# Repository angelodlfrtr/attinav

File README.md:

# Attinav

**Work in progress.** A precision attitude sensor module for cave survey: static "point and
shoot" azimuth and inclination to 0.1°, with the redundancy to tell a good shot from a disturbed
one. This repository covers the sensor module only. The carrier (display, battery, BLE), the laser
and the housing are separate.

## Status

| part | state |
|---|---|
| Hardware Rev B | schematic complete, PCB WIP |
| Firmware | builds, lints and tests clean, never run on hardware |
| Desktop client | builds, lints and tests clean against the built-in simulator, not yet run against hardware |

## Hardware (Rev B)

- STM32U575RGT6 (Cortex-M33, 160 MHz, 1 MiB flash, 768 KiB SRAM)
- 3 × PNI RM3100 magneto-inductive triads (gradiometer: nearby iron shows as disagreement)
- 2 × Murata SCA3300-D01 inclinometer-grade accelerometers
- TDK ICM-42688-P IMU as a motion gate during the integration window
- Pt1000 coil thermometers for temperature-compensated calibration
- USB-C to the host, 8-pin FFC (UART, power, `QUIET`) to the carrier

Design notes and error budget: `hardware/kicad/README.md`. Plan and decisions:
`hardware/kicad/ROADMAP.md`.

## Software

- `software/firmware` — Rust / Embassy firmware: shot engine, on-device Heeb/DistoX
  calibration (14 × 4 shots, up to four temperature sets), quality flags, binary protocol over
  USB CDC and the carrier UART, OTA update with rollback. `README.md`, `PROTOCOL.md`, `OTA.md`.
- `software/client` — Tauri v2 desktop client (React, Redux, Tailwind) to test, calibrate,
  visualise, configure and update the module. Includes a protocol-level simulator, so it runs
  without hardware. `README.md`.

Both projects have a Nix dev shell and a `Makefile`, the root `Makefile` delegates to them:

```sh
make help                            # targets
make check                           # formatting, lints, tests and builds of both projects
make -C software/firmware help
make -C software/client help
```

CI (`.github/workflows/ci.yml`) runs the same targets on every push and pull request, inside the
same Nix shells, plus actionlint and zizmor over the workflows (`make workflows`, root flake).

## License

- Software: AGPL-3.0-only
- Hardware design files: CERN-OHL-S-2.0

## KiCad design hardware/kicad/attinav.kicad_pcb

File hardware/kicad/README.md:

# Attinav hardware — design notes

Design review, error budget and Rev B architecture for the Attinav AHRS module.

**Application:** precise AHRS for cave survey (speleology). Static "point and shoot"
station measurement — azimuth + inclination — not dynamic attitude tracking.
This distinction drives almost every decision below.

**Status:** Rev A reviewed 2026-09-20. Three functional bugs found (see
[Rev A defects](#rev-a-defects)). Rev B architecture proposed but not implemented.

---

## Table of contents

- [Rev A defects](#rev-a-defects)
- [Tooling caveats](#tooling-caveats)
- [Requirements and error budget](#requirements-and-error-budget)
- [Sensor selection rationale](#sensor-selection-rationale)
- [Rev B architecture](#rev-b-architecture)
- [Magnetic hygiene rules](#magnetic-hygiene-rules)
- [System integration](#system-integration)
- [Calibration](#calibration)
- [References](#references)

---

## Rev A defects

Verified against a kicad-cli generated netlist and PCB geometry, not from audit tools.

### Critical — functional bugs

**1. D1/D2 Schottky pair has a floating common node**

`Net-(D1-K)` connects only `D1.K` and `D2.K` — nothing else. D1 is A=GND/K=node,
D2 is A=+3.3V_EXT/K=node. As drawn the pair conducts nothing and protects nothing.

Placement (D1 85.9,138.4; D2 83.3,138.4; near Q1 80.0,134.4 and R4) suggests it was
intended as a rail clamp on `/EN`, which is otherwise a bare MOSFET gate exposed on
J3.12 and J4.2. Note D2's orientation (anode on +3.3V_EXT) is a feed diode, not a
clamp — a positive clamp needs anode on the signal, cathode on the rail.

**2. BOOT0 boot-select jumper is defeated**

NT1 (`NetTie-2_SMD_Pad0.5mm`) hard-shorts `Net-(U1-BOOT0)` to GND with 0 Ω copper.
J1 (pin 2 = +3.3V) feeds BOOT0 through R1 4.7k. Shorting J1 puts 4.7k across a dead
short; BOOT0 stays at ~0 V and never reaches VIH. DFU/system-bootloader entry is
impossible.

*Fix:* replace NT1 with a 10k pull-down. Then check the divider — 4.7k/10k gives only
~2.24 V, so drop R1 to ~1k for margin.

**3. Crystal load caps wrong**

Y1 = YXC **X50328MSB2GI**, 8 MHz, **CL = 20 pF** (confirmed via JLCPCB DB, LCSC
C115962). Required load caps:

```
C = 2 x (CL - Cstray) = 2 x (20 - 4) ~= 33 pF
```

Fitted: **20 pF** (C15/C16) → effective CL ≈ 14 pF. An under-loaded crystal runs
fast, roughly **+60 ppm**, far outside the crystal's own ±10/±20 ppm spec.

*Fix:* C15/C16 → 33 pF.

### Warnings

**4. STM32 (U1) has no local decoupling.** Measured pad-to-pad on the PCB:

| Pin | Nearest same-net cap |
|---|---|
| U1.24 VDD | C11 @ **16.7 mm** |
| U1.36 VDD | C11 @ **10.6 mm** |
| U1.48 VDD | C9 @ **11.9 mm** |
| U1.9 VDDA/VREF+ | C13 @ **11.2 mm** |
| U1.22 VCAP1 | C2 @ 2.26 mm — OK |

C9/C12/C13/C14 sit at x≈78 mm on the left board edge; U1 is at x=93.3 mm — opposite
edges of a 30.5 mm-wide board. Partly mitigated by the stackup (In2 = +3.3V plane,
In3 = GND at 0.1 mm → good plane capacitance), but 100 nF per VDD pin within ~3 mm
is standard practice.

By contrast **U2 (SCHA63T) is done correctly** — all 8 supply pins have caps at
~3.2 mm. The oversight is on U1/U3/U5 only.

VDDA/VREF+ (pin 9) also has no dedicated filtering (no ferrite, no 1 µF + 10 nF).
PB0 is an ADC input reading the LM94021, so this matters.

**5. U3 (RM3100) has no decoupling and no plane.** Nearest +3.3V cap is **24 mm**.
U3 sits at (91.4, 90.4), inside a copper-pour keepout spanning Y 81.28–102.362 on
**all six layers** — deliberate for magnetic cleanliness, but see
[Magnetic hygiene rules](#magnetic-hygiene-rules): this is probably backwards.
Its supply is thin traces only (+3.3V 12.3 mm, GND 9.1 mm, both single-layer F.Cu)
with no local charge reservoir, and the RM3100 is magneto-inductive — it actively
pulses current through its coils.

**6. U5 (TPL5010) 17.3 mm, U4 (LM94021) 5.8 mm** from nearest cap. Both datasheets
call for a local 100 nF.

**7. U1 VBAT (pin 1) floating**, flagged no-connect. ST guidance for STM32F4 is to
tie VBAT to VDD with a 100 nF when no backup battery is used.

**8. No bulk capacitance or protection on +3.3V_EXT.** It arrives on J2.2/J3.3 and
feeds only Q1.S, R4, D2.A — no capacitor at all. C14 is downstream of the PMOS, so
Q1 turn-on dumps inrush into ~13 µF with no gate RC for soft-start.

**9. `/EN` is a bare MOSFET gate on two connectors** (J3.12, J4.2) with only a 10k
pull-up — no series resistor, no ESD clamp (and see defect 1).

### Minor

- **C14 value string wrong**: reads `10uF/50V/20%/XYR/0603`; LCSC C96446 is actually
  Samsung CL10A106MA8NRNC = **10 µF 25 V X5R 0603**. Ordered part is correct and fine
  for 3.3 V; the text has a wrong voltage and a typo ("XYR"). Check C9/C12/C13
  ("50V" → C14663) the same way.
- **U3 has no LCSC/MPN**, and its Datasheet property points to a witmotion.com store
  page for a JY-RM3100 *module*, not the PNI RM3100 datasheet. Also behind the one
  real DRC warning: *"Footprint 'WIT-RM3100' does not match copy in library
  'WIT-rm3100'"*. Resolve before fab.
- **U2 uses property name `MP` not `MPN`** — breaks BOM tooling.
- **Mounting holes inconsistent**: H3 pad tied to GND; H1/H2/H4 explicitly no-connect
  (floating copper).
- **D4 power LED draws ~0.75 mA continuously** on a board built around a 35 nA TPL5010.
- Global `min_clearance`/`min_track_width` are 0.0 in the project, though the Default
  netclass sets 0.2 mm / 0.25 mm so DRC is still meaningful.

### Rev A verified good

- 0 ERC errors, 0 DRC errors, fully routed. No shorted nets. All 12 single-node nets
  are explicit no-connects.
- Geometry fab-friendly: 0.25/0.7 mm tracks, 0.3/0.5 mm via drills, 0.25 mm min pad
  (QFN48 0.5 mm pitch), ~1.6 mm 6-layer stackup.
- Q1 PMOS correctly oriented as high-side switch (S=input, D=load, gate pulled to
  source → default off).
- NRST: 100 nF (C1) + button + internal pull-up per ST guidance; TPL5010 reset gated
  by open solder jumper JP1 (intentional).
- Stackup well considered: In2 (+3.3V) / In3 (GND) 0.1 mm apart for plane capacitance.

---

## Tooling caveats

Konnect MCP audit results on this project are unreliable. Do not trust them without
verification:

- **`run_design_review` verdict "NOT READY"** rests entirely on 7 false decoupling
  errors. It reads **0 pads** from the board and finds only 7 of ~20 power pins.
- **`audit_decoupling`** reports "0/7 power pins have decoupling" while the netlist
  shows 5× 100 nF + 2× 1 µF + 10 µF on +3.3V. It needs board pads for its proximity
  check and silently degrades to "no cap found".
- **`find_orphan_items`: 261 "dangling wire ends"** — all false. Verified
  (81.28, 45.72) is U1 pin 7 (NRST) with a wire correctly landing on it. The tool
  does not resolve pin positions.
- **`get_component_nets` / `trace_from_point` return `net: null`** for pins whose net
  comes from a power symbol rather than a label. They resolve nets from labels only.
- **155 ERC + 45 DRC warnings** were all "library not found / not enabled". Root cause
  (found 2026-11-01): the Konnect MCP server entry in `~/.claude.json` hardcodes
  `KICAD10_SYMBOL_DIR` / `KICAD10_FOOTPRINT_DIR` as Nix store paths, which go stale at
  every rebuild that bumps `kicad-symbols` / `kicad-footprints`. Konnect also does not
  follow KiCad 10's nested `(type "Table")` entry in the user's global lib tables, so
  it had no fallback. **Durable fix (2026-11-02):** the server now starts through
  `sh -c 'eval "$(grep -E "^export KICAD10_(SYMBOL|FOOTPRINT|TEMPLATE|3DMODEL)_DIR=" /run/current-system/sw/bin/kicad-cli)"; exec "$0" "$@"' konnect`,
  reading the current paths from the kicad-cli wrapper at every start. Separately, the
  user's global `sym-lib-table` / `fp-lib-table` held only KiCad 10's nested
  `(type "Table")` entry, which KiCad resolves but Konnect does not follow; they
  were replaced with the flat stock tables (every library via
  `${KICAD10_SYMBOL_DIR}` / `${KICAD10_FOOTPRINT_DIR}`, no store paths). A future KiCad
  release that adds stock libraries needs the template tables copied again. Symptom when it recurs: every stock `lib_id` fails with "no library
  'Device' in the project or global sym-lib-table". Symbols still resolve from the
  embedded cache, so 0-error results on existing sheets remain genuine.

**Reliable method:** generate a real netlist with `kicad-cli` and parse it, and parse
`.kicad_pcb` directly for geometry. Note KiCad 10 writes pad nets as `(net "NAME")`
with no net number — index `[1]`, not `[2]`.

### Konnect schematic-building notes (v0.13.0, learned on the mag sheet)

- **Subagents bind to the Konnect server process alive at spawn.** After an MCP
  reconnect, an already-spawned agent keeps talking to the old process (stale env, old
  toolsets). Respawn agents after any reconnect; never let two agents write one sheet.
- `register_*_library` with global scope **writes into `~/.config/kicad/10.0/*-lib-table`**
  and there is no unregister tool. Do not let agents probe library paths this way.
- `annotate_schematic` must run on the **file that owns the symbols** (child sheet); on
  the root it no-ops. Place with `?` references — explicit numbers are kept and defeat
  per-instance numbering on multi-instanced sheets.
- `move_schematic_component` refuses symbols once they carry multi-instance paths; use
  `move_region`. `edit_sheet` resize does not move sheet pins — re-place them with
  `edit_sheet_pin`, then `validate_sheet_pins`.
- Sheet boxes and pins must land on the 1.27 mm grid or every pin raises
  `endpoint_off_grid`; `batch_delete` by UUID is the only way to remove free text.
- **`kicad-cli sch erc` does not report duplicate reference designators across sheets.**
  A sheet annotated in isolation (MCU sheet, 2026-11-01: U1, R1, C1… colliding with the mag
  and power sheets) passed ERC clean while the netlist merged pins of different parts.
  After every annotation, parse the netlist `(components …)` block and assert every `ref`
  is unique; `annotate_schematic` must be run with the project context so other sheets'
  numbers are reserved.
- `render_schematic_png` without `output` drops a PNG next to the schematic; always pass
  a scratch path. A wire routed straight through a foreign pin silently creates a
  junction (`find_shorted_nets` cannot see unnamed nets) — check coil nodes with
  `trace_from_point` and the `kicad-cli` netlist.

---

## Requirements and error budget

**Target:** 0.1° azimuth, 0.05° inclination. Roughly 2–5× better than a DistoX2.

### The binding constraint

For a tilt-compensated compass, **tilt error is amplified into azimuth error by
tan(magnetic dip)**. At European dip (~63°), tan = **1.96**.

> **The accelerometer must be ~2× better than the azimuth target.**
> For 0.1° azimuth you need ~0.035° of tilt = **0.6 mg**.

This makes the accelerometer, not the magnetometer, the hard problem.

### Field error to heading error

```
heading error (rad) ~= dB / H        H ~= 20 uT horizontal (mid-latitude Europe)

0.1 deg  =>  dB < 35 nT
0.5 deg  =>  dB < 175 nT
```

### Budget

| Term | Contribution |
|---|---|
| Mag noise (3× RM3100, averaged ~5 nT) | 0.014° |
| Mag calibration residual (~20 nT) | 0.057° |
| Tilt error 0.035° × tan 63° | 0.069° |
| Mag↔accel frame misalignment residual | 0.030° |
| Sight-axis alignment | 0.030° |
| **RSS azimuth** | **≈ 0.10°** |
| SCA3300 Mode 4 noise (0.15 mg) | 0.009° |
| Accel offset after temp cal (~1 mg) | 0.057° |
| **RSS inclination** | **≈ 0.05°** |

Nothing here works on factory specs. Per-unit calibration is mandatory.

---

## Sensor selection rationale

### Why the gyro does not buy azimuth

A gyro only replaces the compass if it can **gyrocompass** — resolve Earth's rotation
(15.04°/hr). At 45° latitude the horizontal Earth rate is ~10.6°/hr, so 0.5° of
azimuth needs gyro bias stability around **0.1°/hr**. MEMS parts, SCHA63T included,
are one to two orders of magnitude away.

What a gyro *does* buy:
- Motion/stillness gating during a shot
- **Short attitude transfer** through a magnetically disturbed station. At ~0.28°/√hr
  ARW, carrying azimuth for 1 minute costs ~0.036° — genuinely useful, and a cheap
  part does it. **Do not pay €200 for SCHA63T to do this.**

### Why 3× sensors — and why not for precision

Averaging N sensors cuts *uncorrelated random* error by √N. Three gives 1.73×.
But the design is **not noise-limited**: the RM3100 detects 2.7 nT at 1 Hz, which at
20 µT horizontal is under 0.05° of azimuth noise — already 10× below target.

And **time-averaging is free**: the measurement is static, so 100 samples at 100 Hz
buys √100 = 10× with zero hardware, versus √3 = 1.7× for three chips. Or raise the
RM3100 cycle count.

**The real reasons for redundancy** (and what BRIC5 does — 2× SCA3300-D01 plus
redundant magnetometers, explicitly *"to detect calibration drift, malfunctions, and
magnetic gradients"*):

- **Magnetic gradiometry — of *nearby* iron.** A uniform Earth field reads identically at
  all sensors. Nearby iron — magnetite in the rock beside you, a bolt, a steel carabiner —
  creates a *gradient*. Spatially separated magnetometers that disagree after calibration
  flag the station as disturbed. DistoX users guess at this; measuring it is a real
  capability upgrade.
  **Blind spot:** a large *distant* mass — a steel gate 3 m away, an iron-bearing stratum —
  produces a nearly uniform offset with negligible gradient, and gradiometry cannot see it.
  That case is caught only by the **|B|-vs-IGRF and dip-vs-IGRF** checks. Gradiometry is
  one of three anomaly detectors, not *the* detector.
- **Blunder detection.** You cannot redo a trip.
- **2 detects disagreement; 3 lets you vote** and identify which sensor is wrong.

### Why 3× cheap sensors will NOT work

Averaging fixes *random* error. Cheap sensors fail on *systematic* error:

- Cheap magnetometers (AMR: QMC/HMC5883, LIS3MDL; Hall: BMM150/BMM350) suffer
  hysteresis, nonlinearity and temperature-dependent offset. Three identical parts on
  one board at one temperature drift **the same way** — correlated, so √N does nothing.
- AMR parts need set/reset degauss pulses; miss them and one strong field leaves a
  permanent bias.
- The RM3100's advantage was never noise — it's **linearity, no hysteresis, and gain
  stability**. Averaging cannot recover those.

**3× cheap ≠ 1× good.**

### Why not the DRV425 fluxgate

Verified against the DRV425 datasheet (Rev B, Oct 2025):

| Parameter | Value |
|---|---|
| Noise, **0.1–10 Hz** (compass band) | **17 nT RMS** |
| Noise density @ 1 kHz | 1.5 nT/√Hz |
| Offset | ±2 µT typ, ±8 µT max |
| **Offset drift** | **±5 nT/°C** |
| Gain drift | ±7 ppm/°C |
| Gain error | ±0.04% |
| Linearity error | 0.1% |
| Hysteresis (after ±10 mT sweep) | 1.4 µT |
| Quiescent current | 6 mA typ, 8 mA max @ 3.3 V |
| Compensation loop active after power-on | 70 µs |

The headline 1.5 nT/√Hz is **at 1 kHz** and irrelevant to a compass. The
compass-band figure of 17 nT RMS essentially **ties** the RM3100.

**Power is not the obstacle** — the 70 µs startup makes duty-cycling trivial
(~120 µA average for 3 axes at one shot/minute).

**Offset drift is the obstacle.** ±5 nT/°C gives 0.14° per 10 °C, or 0.27° across a
surface-to-cave transient (25 °C → 6 °C). It is a *magnetic* offset, so no
improvement in electronics touches it. And what closed-loop buys — superb gain
stability — is not what limits a compass, since heading comes from `atan2` of ratios
where common gain error largely cancels.

To beat the RM3100 you would need anti-parallel sensor pairs (6 parts, back-to-back
across the PCB so the sensitive axis reverses), a high-value shunt (~440 Ω instead of
22 Ω, trading the unused ±2 mT range for 20× lower amplifier drift contribution), a
ratiometric multiplexed 24-bit ADC chain, a temperature-stable perpendicular Z mount,
and sequenced duty-cycled power. Not worth it.

**Where the DRV425 would win:** as a dedicated gradiometer, because ±0.04% gain error
and ±7 ppm/°C gain drift mean two parts subtract very cleanly, and a gradiometer only
cares about the difference *changing*. Not needed here — 3× RM3100 already gives
gradiometry.

### RM3100 form factor — important

The RM3100 is a **discrete chipset, not a single package**:

| Component | Size | Qty per suite |
|---|---|---|
| SEN-XY | 6 × 2.1 × 2.21 mm | 2 |
| SEN-Z | 3.88 × 2.98 × **6.35 mm tall** | 1 |
| MagI2C ASIC | 4 × 4 × 0.75 mm, 28-pin MLF | 1 |

- MagI2C must sit **within 10 cm** of the coils.
- **You place the coils, so orthogonality is your responsibility.** PNI specifies a
  5 mil stencil with paste area much smaller than the pad, specifically to limit
  SEN-Z tilt — tilt maps directly to axis misalignment error.
- **SEN-Z is a vertical solenoid that senses the board-normal axis while being
  reflow-soldered flat.** No perpendicular daughtercard. This is the decisive
  advantage over any single-axis in-plane sensor such as the DRV425.
- No successor exists — there is no RM3200. The only variant is **RM3100-CB**, a
  board-mounted vibration-hardened version (50 g RMS, MIL-STD-810H 514.8).

---

## Rev B architecture

| Role | Part | Qty | Rationale |
|---|---|---|---|
| Magnetometer | **PNI RM3100 sensor suite** | **3 sets** | No better option exists. 3 sets = spatial gradiometer + voting |
| Accelerometer | **Murata SCA3300-D01**, Mode 4 | **2** | 0.15 mg RMS, damped element, self-diagnostics. `\|a\|=1g` is a built-in third vote |
| Gyro (optional) | **TDK ICM-42688-P** | 1 | Short attitude transfer + motion gating only |
| Temp at mag coils | **Pt1000 RTD, non-magnetic package** | 3 | The platinum *element* is non-magnetic; **SMD thin-film RTDs often have Ni-barrier terminations** — specify verified non-magnetic terminations or a leaded element. Compensates **gain** tempco only: the MagI2C has no temperature sensor, and PNI states offset is drift-free |
| Temp at accel | **SCA3300 internal die sensor** (TMP117 ×0–1 as board reference only) | — | 18.9 LSB/°C → **0.053 °C resolution**, read in the same SPI frame. Its ±10 °C *absolute* offset is irrelevant — compensation uses a per-unit curve against the reported value. Die temperature is the **correct** variable; an external sensor lags and misses package gradients |
| MCU | **STM32U575RGT6** (LQFP-64, non-Q: LDO only, VCAP; LCSC C5270980). **STM32U585RIT6 is pin-identical** (adds crypto accelerators and 1 MB flash) and stays the drop-in upgrade | 1 | see below — the section is written for the U585; everything applies to the U575 except the crypto peripherals |
| Regulator | **TPS7A2033PDBVR** (300 mA, 7 µVrms, high PSRR; LCSC C2862740, genuine TI only), **EN pin = the FFC `EN` line, high = on**, 100 k pull-down, bench jumper to `+5V` | 1 | **Never a buck** — switching current near a magnetometer is a field source. Replaces Rev A's PMOS gate. Analog rail `+3.3VA` by an **RC split (4.7 Ω + 22 µF), not a ferrite bead** (no magnetic material); the mag AVDD switches stay on `+3V3`. Inputs: `5V_FFC` and USB `VBUS` **Schottky OR-ed** (PMEG2010AEH). One regulator only — the MagI2C's 0.1 V AVDD/DVDD tracking rule forbids separate regulators |
| Protection | **USBLC6-2SC6** on the USB data pair (the port is a JST SH pigtail header, not a steel-shelled USB-C receptacle) + **TVS on both 5 V inputs** (SMF5V0A on `5V_FFC` and on `VBUS`) | 1 + 2 | Both at the rear, both silicon — no magnetic concern. Previously missing |
| Decoupling at coils | **Non-magnetic MLCC** (Cu/Ag termination) | — | Standard MLCCs have ferromagnetic Ni barrier terminations |

**Dropped:** SCHA63T (€200 for gyro performance that contributes nothing to static
precision, and its accelerometer is superseded by the SCA3300). DRV425 (see above).

### Accelerometer: SCA3300 over ADXL355

Verified from the SCA3300-D01 datasheet Table 2 (Doc. 3165 Rev 3):

| | **SCA3300-D01 (Mode 4)** | ADXL355 |
|---|---|---|
| Noise | 0.15 mg RMS ≈ **0.0086°** | 25 µg/√Hz ≈ 0.0045° |
| Offset temp dependency, −40…+125 °C | **±10 mg (±0.57°) X/Y**, ±15 mg Z — bounded total | ±0.15 mg/°C ≈ 0.008°/°C |
| Total offset incl. lifetime drift | ±20 mg (±1.15°) | 10-yr repeatability ±3.5 mg (0.2°) X/Y |
| Sensitivity error / tempco | ±0.7% / ±0.3% | — |
| Linearity | ±1 mg over ±1 g | — |
| Cross-axis | ±1% | ~±1% |
| Mechanical damping | **Yes** | No |
| Self-diagnostics | **Extensive** | Minimal |
| Range | **±1.5 g** (Mode 4) — right-sized for tilt | ±2/4/8 g |
| Bandwidth / settling (Mode 4) | 10 Hz / 100 ms | — |

Reasons SCA3300 wins here:

1. **Mechanically damped element.** Caving means knocks; an undamped MEMS rings after
   a jolt. Mode 4's 10 Hz / 100 ms settling matches the "stop moving, take the shot"
   workflow.
2. **±1.5 g range** — you only ever measure ±1 g, so full scale is on the useful signal.
3. **Bounded offset-drift spec** over the whole range rather than a per-°C slope.
4. **The ADXL355 is sensitive to PCB stress and thermal gradients** — one reported
   measurement showed 3.4–4.2 mg/°C on Z with a gradient across the package, over 20×
   the datasheet figure. A handheld going from a warm pack into a 6 °C cave is exactly
   that scenario.
5. It is what BRIC4/BRIC5 ship, in this exact application.

The ADXL355's lower noise density buys nothing, because the design is not noise-limited.

**Orientation rule:** the SCA3300's offset temperature dependency is ±10 mg on X/Y but
**±15 mg on Z**. Inclination of the sight axis is asin(a_sight / |a|), dominated by the
error on the axis *along* the sight line. So mount each SCA3300 with **the sight axis on
X or Y, never Z** — a free 1.5× on the budget's largest term.

**Refinement — rotate the pair.** That rule is right for normal legs, but on a steep pitch
shot the *perpendicular* axes dominate the inclination error, and one of them must be Z.
Mount the two SCA3300s **rotated 90° about the sight axis** relative to each other: every
shot geometry then has at least one sensor with good axes in the critical direction, and
any common-mode bias becomes a visible disagreement instead of a shared error. Costs
nothing; calibration absorbs the frames.

**Temperature comes from the die.** The SCA3300's internal sensor (18.9 LSB/°C,
0.053 °C resolution) is read in the same SPI frame and measures what the MEMS actually
experiences. Use it for compensation; an external TMP117 is redundant for this purpose.

### MCU: STM32U585

> **Fitted part (decided 2026-11-01): STM32U575RGT6**, LCSC C5270980 — the same die family,
> package and non-Q (LDO-only) pinout, minus the crypto accelerators and with 1 MB flash
> instead of 2 MB. Chosen because the U585RIT6 is out of stock at LCSC and would need
> consignment. Everything below applies to the U575 except the cryptographic peripherals;
> the U585RIT6 remains a zero-change upgrade.

The F401 is functionally adequate but wrong for this instrument.

| | STM32F401CE (Rev A) | **STM32U585 (Rev B)** |
|---|---|---|
| Core | Cortex-M4F @ 84 MHz | Cortex-M33 @ 160 MHz, DSP, FPU, TrustZone |
| Flash | 512 KB | **2 MB, dual-bank** |
| SRAM | 96 KB | **786 KB** |
| Power class | performance line | **ultra-low-power, <30 µA/MHz**. **LDO mode, no SMPS inductor on the board** — the "Q" part's SMPS is a switching regulator, which the no-buck rule forbids, and its run-mode saving is moot because the core sleeps (LPBAM) during integration. Prefer a non-Q part; if only a Q variant is in stock, run it LDO-only per AN5373 (VDDSMPS/VLXSMPS/VSSSMPS → VSS, 2.2 µF + 100 nF on VDD11, no inductor, `REGSEL = 0`). The rule is about the inductor, not the silicon |
| Autonomous DMA | — | **LPBAM** |

- **786 KB SRAM** makes the full 56-shot nonlinear least-squares calibration solve
  feasible on-device; impossible in 96 KB.
- **LPBAM (Low Power Background Autonomous Mode)** lets LPDMA clock SPI transactions
  and collect hundreds of averaged samples *while the M33 sleeps*. Precision here
  comes from averaging, so this makes averaging nearly free.
- **Dual-bank flash** — keep calibration in the bank you are not reflashing.
- LQFP64 comfortably fits ~30 GPIO: shared SPI + 3× MagI2C CS/DRDY + 2× SCA3300 CS +
  I2C + host interface + SWD.

> **Design decision: on-device calibration is a requirement, not a fallback.**
> A phone could host the solve instead (see
> [Calibration with a smartphone](#calibration-with-a-smartphone)), which would let the
> MCU shrink to a U535/U545 or even stay on the F401 — the DistoX2 does its whole job on
> a Cortex-M0. **We are deliberately not doing that.** The module solves its own
> calibration so it can be recalibrated and self-checked underground with no phone, no
> app version dependency, and no reliance on a BLE link. The phone becomes an optional
> UI and reference-data source rather than a required part of the loop. The U585's
> 786 KB SRAM and 160 MHz are sized for that, and the resulting firmware is the main
> consumer of both.

**TPL5010:** keep only if the module wakes itself. The carrier board already owns power
gating via `/EN` (now the LDO's EN pin), so if the carrier owns the duty cycle, drop the timer.

---

## Magnetic hygiene rules

Scale reference: **10 mA at 10 mm ≈ 200 nT**. Against 20 µT horizontal that is
**0.6° of azimuth** — the entire error budget from one stray milliamp-scale loop.

1. **Reverse the pour keepout.** Copper is diamagnetic (χ ≈ −10⁻⁵) and does not
   distort a DC field. The reason to fear planes near a magnetometer is *current in
   them*, not the metal — and removing the plane forced Rev A's supply and return into
   long open loops. Keep a ground plane under the magnetometers; route each MagI2C's
   supply/return as a tight pair with decoupling **at the MagI2C ASIC, not at the coils**
   (PNI: *"keep capacitors, especially tantalum capacitors, far away from the sensor
   coils"*); keep
   unrelated return currents out of the region.
2. **Surface finish: OSP. NOT ENIG.** Electroless *Nickel* Immersion Gold deposits
   3–6 µm of ferromagnetic nickel on every exposed pad. Rev A has `copper_finish "None"`
   — unspecified, so the fab chooses, and for 6-layer that is usually ENIG. TI states the
   same requirement for the DRV425: *"select non-magnetizable materials for the PCB and
   passives in the direct vicinity"*.
   **At JLCPCB the choice is forced and favourable:** 6-layer boards are offered only in
   **OSP or ENIG** — no HASL (planarity), no immersion silver. OSP is an organic coating
   with no metal at all, the flattest finish for the 0.4 mm-pitch MLF, and carries no
   surcharge. Caveats: ~6-month shelf life and bare copper on any later hand rework, so
   **order fab and assembly together** and don't stockpile bare boards.
3. **Non-magnetic hardware**: brass, titanium or nylon M2. Rev A's H1/H2 sit 12.3 mm
   from the magnetometer — a steel screw there is a large hard-iron source *and* a
   removable one that voids calibration when retorqued or swapped.
4. **Spread the 3 coil sets as widely as the board allows** — simultaneously the
   gradiometer baseline and the mutual-coupling mitigation.
5. **Time-multiplex the three RM3100s.** They actively drive their coils. At CC=200 a
   3-axis read is ~5 ms, so three sequential sets is ~15 ms; hand tremor over 15 ms is
   negligible, so the gradient measurement stays valid.
6. **LDO, never a switching regulator.**
7. **No crystal at all.** The can lid is typically ferromagnetic, and nothing needs one:
   SPI runs from the internal oscillator, **USB FS runs crystal-free on HSI48 + CRS**, and
   the **carrier owns wall-clock time** (it has BLE/phone) and sends it at power-up — the
   module keeps relative time only, so no RTC crystal either.
8. **Quiesce the board during the read** — LEDs off, no SPI traffic at the sampling
   instant. A constant current is calibratable; a blinking one is not.

### Calibratable vs. not

| Calibratable (hard/soft iron) | NOT calibratable |
|---|---|
| MLCC nickel barrier terminations | Time-varying currents |
| ENIG pads | Temperature-dependent drift |
| A permanently-fitted screw | Anything that moves relative to the sensor |
| Coil non-orthogonality (3×3 matrix absorbs it) | Mechanical instability of the mount |

Design so the uncalibratable set is minimised.

### Mechanical

- **SEN-Z is 6.35 mm tall** — taller than anything on Rev A (U2 at 4.8 mm). Check the
  enclosure.
- **Board area**: 9 coils + 3 ASICs + 2× SCA3300 (8.6 × 7.6 mm each) is a lot for
  30.48 × 58.42 mm. Expect to grow the board or go to a two-board stack.
- **Alignment to the sighting axis** is a precision mechanical problem. Everything
  above yields the attitude of the *PCB*; what you survey is the laser axis. If the
  module is removable, you need a kinematic mount or a documented re-calibration policy.
- **Conformal coat** — 100% humidity and mud. Costs nothing magnetically.

---

## System integration

The instrument is a **three-board stack**:

| Board | Contents |
|---|---|
| **AHRS module** (this design) | Magnetometers, accelerometers, gyro, MCU |
| **Carrier / UI board** | BLE radio, screen, buttons, battery, power management |
| **Laser board** | Laser rangefinder for distance |

Once the sensors sit in a real instrument, **magnetic hygiene stops being a PCB problem
and becomes a system mechanical problem.** This is the largest remaining risk in the
design.

### Cross-board magnetic threats

Same scale reference as above — 10 mA at 10 mm ≈ 200 nT ≈ 0.6° of azimuth.

| Source | Mechanism | Rough impact |
|---|---|---|
| **Speaker / buzzer / vibration motor** | **Permanent magnet** | Catastrophic — mT at cm range. Must be absent or very far |
| **Laser module** | Metal can + 30–50 mA pulsed drive + APD bias boost converter | ~270 nT at 30 mm → **0.8°** |
| **Battery (Li-ion)** | Steel case (hard iron) + large discharge current | Calibratable *if fixed* — see below |
| **Screen** | Steel frame + backlight boost converter | Hard iron, plus in-band envelope whenever brightness changes |
| **BLE radio** | RF itself is far out of band, but **supply current pulses at the packet rate** (~10 mA for ~1 ms) | ~100 nT at 20 mm → **0.3°**, transient |
| **Buttons** | Steel domes | Hard iron, calibratable if fixed |
| **Inter-board cable** | Supply/return loop area | Route as a tight pair, or flex with adjacent ground |

**Stack ordering is a first-class design decision.** Put the AHRS board at the far end
from battery, screen and laser, with the magnetometer coils at the far end of the AHRS
board.

### The magnetic quiet window

A **system-level** requirement, not a board-level one. The AHRS module must be able to
demand silence from the rest of the instrument — either a hardware `MEASURE` line it
asserts, or a protocol message the carrier honours.

During the window:

- BLE **not transmitting**
- Backlight off, or held in a fixed state
- Laser off
- No buzzer or vibration motor
- Converters in a fixed load state

Sequence one shot as:

1. User aims, presses the button
2. **Quiet window** → magnetometer + accelerometer capture *(the precision-critical step)*
3. Laser fires for distance
4. Display update + BLE transmit

Steps 2 and 3 must not overlap. Verify the instrument did not move between them using
the gyro — **this is the clearest justification for carrying a gyro at all.**

### Calibrate the assembled instrument, never the bare board

Every piece of ferromagnetic material in the assembly — screen frame, battery case,
laser can, screws — is hard/soft iron **fixed in the sensor frame**. That makes it
calibratable, but only *as an assembly*.

- Any disassembly potentially voids calibration.
- **A removable battery is a calibration hazard.** If the cell can shift position or be
  swapped for a different one, its hard-iron signature changes. Prefer a captive cell,
  or characterise the variation and fold it into the error budget.
- Store calibration in the AHRS module's flash but tag it with the **assembly serial**.
  Firmware should warn or refuse if the module finds itself in a different carrier.

### Module interface requirements

- Expose **both raw (uncalibrated) counts and calibrated output**. Calibration — whether
  solved on-device or on a phone — operates on raw data.
- Honour the quiet-window signal.
- Allow settling time after `/EN` power-up before measuring. The SCA3300 in Mode 4 needs
  100 ms output settling regardless.

---

## Calibration

This is where the accuracy actually comes from. The parts get you a platform capable
of 0.1°; only calibration realises it.

- Implement the **full Heeb/DistoX model**: magnetometer offset + 3×3 matrix (the
  matrix absorbs coil non-orthogonality), accelerometer offset + 3×3, **and the
  rotation between the mag and accel frames**. That last term is mandatory with
  separate packages — die-to-package rotation is often ±1–3° per part.
- Procedure: ~56 shots in 14 groups of 4 roll angles (DistoX2 convention).
- **Calibrate at 2–3 temperatures and interpolate.** Neither sensor hits target on
  factory calibration — the SCA3300's total offset error including lifetime drift is
  ±1.15°.
- **Calibrate at cave temperature with thermal soak**, not in a warm room. Caves are
  thermally benign (4–12 °C, very stable); the enemy is the surface→cave transient.
- Store with **checksum + calibration ID + date** in a dedicated flash bank, so every
  survey records which calibration produced it.

### Use the redundancy actively in firmware

Flag a shot when:

- the 3 magnetometers disagree after calibration → **magnetic gradient → *nearby* iron**
- `|a| != 1 g` → accelerometer fault or motion
- `|B| !=` the WMM/IGRF value for the cave's location → **uniform disturbance → *distant*
  iron or regional anomaly** — invisible to the gradiometer
- computed dip ≠ IGRF dip → same, and a cross-check on the mag↔accel calibration
- the gyro reports motion during the integration window

The first and third are **complementary, not redundant**: gradiometry sees what is near
you; the IGRF magnitude check sees what is far away. Shipping one without the other
leaves a class of anomaly undetected.

### Calibration with a smartphone

The solve runs **on-device** by design (see [MCU: STM32U585](#mcu-stm32u585)). The phone
is an optional complement, not part of the required loop.

**What a phone genuinely contributes:**

| Capability | Value |
|---|---|
| **GPS position + date → IGRF/WMM** | Expected \|B\|, dip I, declination D at the cave |
| **\|B\| check** | Validates magnetometer **scale factor** absolutely, no Helmholtz coil — to ~±150 nT ≈ 0.3% |
| **Dip check** | After calibration, computed dip must match IGRF. The classic DistoX calibration quality check |
| **Declination** | Magnetic → true north for the survey. Essential, not optional |
| **Precise UTC** | Logging, and the IGRF epoch |
| **Guidance UI** | Walk the user through 56 shots / 14 groups / 4 roll angles, show live residuals, flag under-sampled orientations |
| **Validation** | Display residual and solve conditioning, and **refuse a bad calibration** |
| **Temp-cal logging** | Log sensors + temperature over hours as the instrument warms and cools |

Guidance and validation matter more than they sound: the dominant calibration failure
mode is poor orientation coverage, and calibration *checking* is a known real-world gap
(see Perne in [References](#references)).

For better than IGRF on \|B\|, pull same-day data from the nearest INTERMAGNET
observatory — Chambon-la-Forêt (CLF) for France. That gets to tens of nT rather than ~150.

**What a phone can NOT do: be a reference.** Phone magnetometers are consumer AMR/Hall
parts (AK09918, BMM150/350) inside a case full of steel, speaker magnets, MagSafe
magnets, vibration motors and switching converters. Typical heading accuracy 3–15° —
30–150× worse than the 0.1° target. Its accelerometer is likewise ±30–50 mg. **The phone
is a host and a data source, never a standard.**

### Absolute references

None of these come from a phone alone.

- **Azimuth — surveyed baseline.** Two permanent marks whose azimuth is determined once
  with survey-grade GNSS or a total station, then reused indefinitely as the check
  baseline.
- **Azimuth — solar sighting.** With precise time and position from the phone, the sun's
  azimuth is computable to arcseconds. Sight through a filter or use shadow projection on
  a levelled mount. Cheap, needs no survey equipment, and you are outdoors at the
  entrance anyway.
- **Inclination — the flip method.** Measure, rotate 180° about the vertical, measure
  again. The readings must be equal and opposite; any common component is offset. Fully
  self-referencing, no equipment.
- **Magnetometer offset vs. gain — also the flip principle.** Rotating 180° flips the
  field in the sensor frame but not the offset, which separates the two. This is exactly
  what the 4-roll-angle DistoX procedure exploits.
- **Temperature coefficients.** A cooler with ice packs plus a low oven gives 3 points
  across 0–30 °C, with the SCA3300 die sensor / Pt1000 logging actual temperature. Crude but
  sufficient.

---

## References

**Parts**
- [PNI RM3100](https://www.pnisensor.com/rm3100/) ·
  [RM3100-CB](https://www.pnisensor.com/rm3100-cb/) ·
  [RM3100/RM2100 Sensor Suite User Manual V11.0](https://www.pnicorp.com/wp-content/uploads/RM3100-RM2100-Sensor-Suite-User-Manual-V11.0.pdf) ·
  [PNI magnetic sensor comparison chart](https://www.pnicorp.com/wp-content/uploads/0123_Mag_Sensor_Chart.pdf)
- [Murata SCA3300-D01 datasheet (Doc 3165 Rev 3)](https://www.murata.com/-/media/webrenewal/products/sensor/pdf/datasheet/datasheet_sca3300-d01.ashx?la=en-us&cvid=20190620010315610400)
- [Murata SCL3300 (inclinometer variant)](https://www.murata.com/en-us/products/sensor/inclinometer/overview/lineup/scl3300)
- [Analog Devices ADXL355](https://www.analog.com/en/products/adxl355.html) ·
  [ADXL355 thermal-gradient drift discussion](https://ez.analog.com/mems/f/q-a/109322/adxl355-strong-temperature-drift-on-z-axis-with-heater)
- [TI DRV425 datasheet (Rev B, Oct 2025)](https://www.ti.com/lit/ds/symlink/drv425.pdf) ·
  [DRV425 independent offset-stability testing, CTU Prague](https://www.researchgate.net/publication/330255637_Testing_and_application_of_an_integrated_fluxgate_sensor_DRV425)
- [STM32U585 datasheet (DS13086)](https://www.mouser.com/pdfDocs/stm32u585ai.pdf)

**Cave survey instruments and calibration**
- [Beat Heeb — The Next Generation of the DistoX Cave Surveying Instrument](https://paperless.bheeb.ch/download/DistoX2.pdf)
- [Marco Corvi — DistoX2, SAP5 and BRIC4 comparison](https://ia801800.us.archive.org/32/items/disto-xsap-bric-20200302/DistoXSapBric-20210329.pdf)
- [BRIC survey — design history](https://www.bricsurvey.com/about)
- [Matija Perne — DistoX calibration tools and the need for calibration checking (arXiv)](https://arxiv.org/pdf/2102.09891)

**Geomagnetic reference data**
- [NOAA/NCEI World Magnetic Model (WMM)](https://www.ncei.noaa.gov/products/world-magnetic-model) — field model, coefficients and source code
- [IAGA IGRF](https://www.ncei.noaa.gov/products/international-geomagnetic-reference-field) — higher-order reference field model
- [INTERMAGNET](https://intermagnet.org/) — observatory data; Chambon-la-Forêt (CLF) is the French station

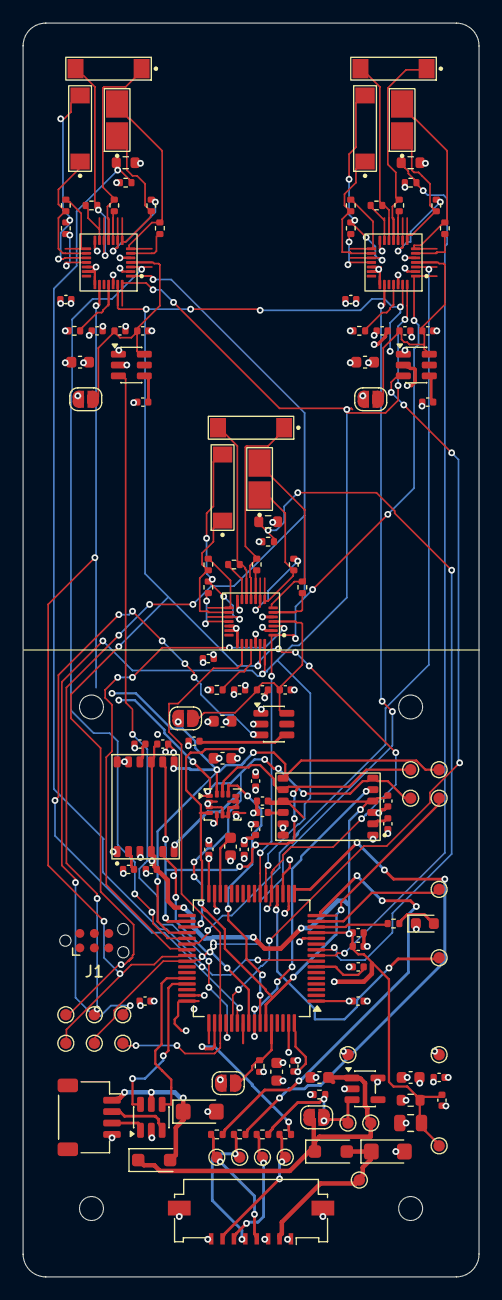
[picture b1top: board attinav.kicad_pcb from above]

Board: 6 copper layers, 40.0 x 110.0 mm, 139 parts (0 on the bottom side), 96 nets.

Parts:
C1, C7, C13: 1n/X7R; C_0402_1005Metric
C2, C8, C14, C25, C41: 1u/X7R; C_0402_1005Metric
C3, C4, C5, C9, C10, C11, C15, C16, C17, C27, C34, C35, C36, C37, C39, C40, C43, C45, C46, C47, C48, C49, C50, C51, C52, C55: 100n/X7R; C_0402_1005Metric
C6, C12, C18, C24, C28: 10u/X7R; C_0603_1608Metric
C26: 22u/X7R; C_0805_2012Metric
C38, C42: 4.7u/X7R; C_0603_1608Metric
C53: 10n/X7R; C_0402_1005Metric
C54: 2.2u/X7R; C_0603_1608Metric
D2: LED GREEN; LED_0603_1608Metric
D5, D7: PMEG2010AEH; D_SOD-123F
D6, D8: SMF5V0A; D_SMF
H1, H2: DowelHole; MountingHole_2.1mm
H3, H4: MountingHole; MountingHole_2.1mm
J1: Tag-Connect_TC2030-IDC-NL_2x03_P1.27mm_Vertical
J3: USB pigtail JST SH 4p; JST_SH_SM04B-SRSS-TB_1x04-1MP_P1.00mm_Horizontal
J4: FFC 8p 1.0mm flip-lock; Molex_200528-0080_1x08-1MP_P1.00mm_Horizontal
JP1, JP2, JP3, JP5, JP6: SolderJumper_2_Open; SolderJumper-2_P1.3mm_Open_RoundedPad1.0x1.5mm
L1, L4, L7: Sen-Z-f; PNI_Sen-Z-f
L2, L3, L5, L6, L8, L9: Sen-XY-f; PNI_Sen-XY-f
R1, R9, R17: 10k/0.1%; R_0402_1005Metric
R2, R10, R18: 33k/1%; R_0402_1005Metric
R3, R4, R5, R6, R7, R8, R11, R12, R13, R14, R15, R16, R19, R20, R21, R22, R23, R24: 121R/1%; R_0402_1005Metric
R27: 100k/1%; R_0402_1005Metric
R28: 4.7R/1%; R_0603_1608Metric
R29: 10k/1%; R_0402_1005Metric
R30: 1k/1%; R_0402_1005Metric
R33, R34, R35, R36: 100R/1%; R_0402_1005Metric
TH1, TH2, TH3: PT1000; R_0603_1608Metric
TP1: TP_FFC_TX; TestPoint_Pad_D1.0mm
TP2: TP_FFC_RX; TestPoint_Pad_D1.0mm
TP3: TP_FFC_EN; TestPoint_Pad_D1.0mm
TP4: TP_FFC_QUIET; TestPoint_Pad_D1.0mm
TP6: TP_+5V; TestPoint_Pad_D1.0mm
TP7: TP_+3.3V; TestPoint_Pad_D1.0mm
TP8: TP_+3.3VA; TestPoint_Pad_D1.0mm
TP9: TP_EN; TestPoint_Pad_D1.0mm
TP10: TP_GND; TestPoint_Pad_D1.0mm
TP14: TP_SCLK; TestPoint_Pad_D1.0mm
TP15: TP_MOSI; TestPoint_Pad_D1.0mm
TP16: TP_MISO; TestPoint_Pad_D1.0mm
TP17: TP_DRDY1; TestPoint_Pad_D1.0mm
TP18: TP_DRDY2; TestPoint_Pad_D1.0mm
TP19: TP_DRDY3; TestPoint_Pad_D1.0mm
TP20: TP_PA1; TestPoint_Pad_D1.0mm
TP21: TP_PA4; TestPoint_Pad_D1.0mm
TP23: TP_ACC_SCLK; TestPoint_Pad_D1.0mm
TP24: TP_ACC_MOSI; TestPoint_Pad_D1.0mm
TP25: TP_ACC_MISO; TestPoint_Pad_D1.0mm
TP26: TP_IMU_INT; TestPoint_Pad_D1.0mm
TP27: TP_FFC_5V; TestPoint_Pad_D1.0mm
U1, U3, U5: TPS22917DBV; SOT-23-6
U2, U4, U6: MagI2C 13156; PNI_MagI2C_MLF-28_4x4mm_P0.4mm_NoEP
U7: USBLC6-2SC6; SOT-23-6
U8: TPS7A2033PDBVR; SOT-23-5
U9: STM32U575RGTx; LQFP-64_10x10mm_P0.5mm
U10: ICM-42688-P; LGA-14_3x2.5mm_P0.5mm_LayoutBorder3x4y
U13, U14: SCA3300-D01; Murata_SCA3300-D01

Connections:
+3.3VA: C26.2, C27.2, C40.1, C41.1, C45.2, C46.1, C49.2, C50.1, R28.2, TP8.1 (1_1), U9.13 (VDDA), U13.4 (VDD), U13.9 (DVIO), U14.4 (VDD), U14.9 (DVIO)
+3V3: C4.1, C5.1, C6.1, C10.1, C11.1, C12.1, C16.1, C17.1, C18.1, C24.2, C25.2, C34.1, C35.1, C36.1, C37.1, C38.1, C39.1, C53.1, C54.2, C55.2, JP1.1 (A), JP2.1 (A), JP3.1 (A), JP6.1 (A), R1.1, R9.1, R17.1, R28.1, TP7.1 (1_1), U1.1 (VIN), U2.14 (DVDD), U2.26 (DVDD), U3.1 (VIN), U4.14 (DVDD), U4.26 (DVDD), U5.1 (VIN), U6.14 (DVDD), U6.26 (DVDD), U8.5 (OUT), U9.1 (VBAT), U9.19 (VDD), U9.32 (VDD), U9.48 (VDDUSB), U9.64 (VDD), U10.5 (VDDIO), U10.8 (VDD)
+5V: C28.2, D5.1 (K), D7.1 (K), JP5.1 (A), TP6.1 (1_1), U8.1 (IN)
/5V_FFC: D5.2 (A), D6.1 (A1), J4.2, TP27.1 (1_1)
/ACC_MISO: TP25.1 (1_1), U9.35 (PB14), U10.1 (AP_SDO/AP_AD0), U13.6 (MISO), U14.6 (MISO)
/ACC_MOSI: TP24.1 (1_1), U9.36 (PB15), U10.14 (AP_SDA/AP_SDIO/AP_SDI), U13.7 (MOSI), U14.7 (MOSI)
/ACC_SCLK: TP23.1 (1_1), U9.34 (PB13), U10.13 (AP_SCL/AP_SCLK), U13.8 (SCK), U14.8 (SCK)
/AVDD_EN1: U1.3 (ON), U9.52 (PC11)
/AVDD_EN2: U3.3 (ON), U9.53 (PC12)
/AVDD_EN3: U5.3 (ON), U9.54 (PD2)
/CS_ACC1: U9.56 (PB4), U13.5 (CSB)
/CS_ACC2: U9.57 (PB5), U14.5 (CSB)
/CS_IMU: U9.58 (PB6), U10.12 (AP_CS)
/CS_MAG1: U2.3 (SSN/SA0), U9.37 (PC6)
/CS_MAG2: U4.3 (SSN/SA0), U9.38 (PC7)
/CS_MAG3: U6.3 (SSN/SA0), U9.39 (PC8)
/DRDY_MAG1: TP17.1 (1_1), U2.23 (DRDY), U9.40 (PC9)
/DRDY_MAG2: TP18.1 (1_1), U4.23 (DRDY), U9.41 (PA8)
/DRDY_MAG3: TP19.1 (1_1), U6.23 (DRDY), U9.51 (PC10)
/EN: JP5.2 (B), R27.2, R33.2, TP9.1 (1_1), U8.3 (EN)
/IMU_INT: TP26.1 (1_1), U9.59 (PB7), U10.4 (INT1/INT)
/INTERFACE/FFC_EN: J4.6, R33.1, TP3.1 (1_1)
/INTERFACE/FFC_QUIET: J4.7, R34.1, TP4.1 (1_1)
/INTERFACE/FFC_RX: J4.5, R35.1, TP2.1 (1_1)
/INTERFACE/FFC_TX: J4.4, R36.1, TP1.1 (1_1)
/MAG1/AVDD_SW: C2.1, C3.1, JP1.2 (B), U1.6 (VOUT), U2.4 (AVDD)
/MAG2/AVDD_SW: C8.1, C9.1, JP2.2 (B), U3.6 (VOUT), U4.4 (AVDD)
/MAG3/AVDD_SW: C14.1, C15.1, JP3.2 (B), U5.6 (VOUT), U6.4 (AVDD)
/MCU/BOOT0: JP6.2 (B), R29.2, U9.60 (PH3)
/MCU/NRST: C43.2, U9.7 (NRST)
/MCU/TP_PA1: TP20.1 (1_1), U9.15 (PA1)
/MCU/TP_PA4: TP21.1 (1_1), U9.20 (PA4)
/MCU/USB_DM: U7.4 (I/O2), U9.44 (PA11)
/MCU/USB_DP: U7.6 (I/O1), U9.45 (PA12)
/QUIET: R34.2, U9.50 (PA15)
/SPI_MISO: TP16.1 (1_1), U2.28 (MISO/SA1), U4.28 (MISO/SA1), U6.28 (MISO/SA1), U9.22 (PA6)
/SPI_MOSI: TP15.1 (1_1), U2.1 (MOSI/SDA), U4.1 (MOSI/SDA), U6.1 (MOSI/SDA), U9.23 (PA7)
/SPI_SCLK: TP14.1 (1_1), U2.27 (SCLK/SCL), U4.27 (SCLK/SCL), U6.27 (SCLK/SCL), U9.21 (PA5)
/TEMP_MAG1: R1.2, TH1.1, U9.8 (PC0)
/TEMP_MAG2: R9.2, TH2.1, U9.9 (PC1)
/TEMP_MAG3: R17.2, TH3.1, U9.10 (PC2)
/UART_RX: R35.2, U9.17 (PA3)
/UART_TX: R36.2, U9.16 (PA2)
/VBUS: D7.2 (A), D8.1 (A1), J3.1, U7.5 (VBUS)
GND: C1.1, C2.2, C3.2, C4.2, C5.2, C6.2, C7.1, C8.2, C9.2, C10.2, C11.2, C12.2, C13.1, C14.2, C15.2, C16.2, C17.2, C18.2, C24.1, C25.1, C26.1, C27.1, C28.1, C34.2, C35.2, C36.2, C37.2, C38.2, C39.2, C40.2, C41.2, C42.1, C43.1, C45.1, C46.2, C47.1, C48.1, C49.1, C50.2, C51.1, C52.1, C53.2, C54.1, C55.1, D2.1 (K), D6.2 (A2), D8.2 (A2), J3.4, J4.1, J4.3, J4.8, J4.MP (MountPin), R2.1, R10.1, R18.1, R27.1, R29.1, TH1.2, TH2.2, TH3.2, TP10.1 (1_1), U1.2 (GND), U2.2 (RES), U2.5 (AVSS), U2.19 (DVSS), U2.20 (RES), U2.22 (I2CEN), U3.2 (GND), U4.2 (RES), U4.5 (AVSS), U4.19 (DVSS), U4.20 (RES), U4.22 (I2CEN), U5.2 (GND), U6.2 (RES), U6.5 (AVSS), U6.19 (DVSS), U6.20 (RES), U6.22 (I2CEN), U7.2 (GND), U8.2 (GND), U9.12 (VSSA), U9.18 (VSS), U9.31 (VSS), U9.47 (VSS), U9.63 (VSS), U10.2 (RESV), U10.3 (RESV), U10.6 (GND), U10.7 (RESV), U10.9 (INT2/FSYNC/CLKIN), U10.10 (RESV), U10.11 (RESV), U13.1 (AVSS), U13.3 (RESERVED), U13.11 (DVSS), U13.12 (EMC_GND), U14.1 (AVSS), U14.3 (RESERVED), U14.11 (DVSS), U14.12 (EMC_GND)
unnamed: D2.2 (A), R30.2
unnamed: J3.2, U7.3 (I/O2)
unnamed: J3.3, U7.1 (I/O1)
unnamed: L1.1 (1_POL), R4.1, U2.8 (ZINN)
unnamed: L4.1 (1_POL), R12.1, U4.8 (ZINN)
unnamed: L7.1 (1_POL), R20.1, U6.8 (ZINN)
unnamed: C1.2, U1.4 (CT)
unnamed: R2.2, U2.25 (REXT)
unnamed: R5.2, U2.18 (XDRVN)
unnamed: R8.2, U2.15 (XDRVP)
unnamed: L3.2, R5.1, U2.17 (XINN)
unnamed: L3.1, R8.1, U2.16 (XINP)
unnamed: R3.2, U2.13 (YDRVN)
unnamed: R6.2, U2.10 (YDRVP)
unnamed: L2.2, R3.1, U2.12 (YINN)
unnamed: L2.1, R6.1, U2.11 (YINP)
unnamed: R4.2, U2.9 (ZDRVN)
unnamed: R7.2, U2.6 (ZDRVP)
unnamed: L1.2, R7.1, U2.7 (ZINP)
unnamed: C7.2, U3.4 (CT)
unnamed: R10.2, U4.25 (REXT)
unnamed: R13.2, U4.18 (XDRVN)
unnamed: R16.2, U4.15 (XDRVP)
unnamed: L6.2, R13.1, U4.17 (XINN)
unnamed: L6.1, R16.1, U4.16 (XINP)
unnamed: R11.2, U4.13 (YDRVN)
unnamed: R14.2, U4.10 (YDRVP)
unnamed: L5.2, R11.1, U4.12 (YINN)
unnamed: L5.1, R14.1, U4.11 (YINP)
unnamed: R12.2, U4.9 (ZDRVN)
unnamed: R15.2, U4.6 (ZDRVP)
unnamed: L4.2, R15.1, U4.7 (ZINP)
unnamed: C13.2, U5.4 (CT)
unnamed: R18.2, U6.25 (REXT)
unnamed: R21.2, U6.18 (XDRVN)
unnamed: R24.2, U6.15 (XDRVP)
unnamed: L9.2, R21.1, U6.17 (XINN)
unnamed: L9.1, R24.1, U6.16 (XINP)
unnamed: R19.2, U6.13 (YDRVN)
unnamed: R22.2, U6.10 (YDRVP)
unnamed: L8.2, R19.1, U6.12 (YINN)
unnamed: L8.1, R22.1, U6.11 (YINP)
unnamed: R20.2, U6.9 (ZDRVN)
unnamed: R23.2, U6.6 (ZDRVP)
unnamed: L7.2, R23.1, U6.7 (ZINP)
unnamed: R30.1, U9.14 (PA0)
unnamed: C42.2, U9.30 (VCAP)
unnamed: C48.2, U13.2 (A_EXTC)
unnamed: C47.2, U13.10 (D_EXTC)
unnamed: C52.2, U14.2 (A_EXTC)
unnamed: C51.2, U14.10 (D_EXTC)

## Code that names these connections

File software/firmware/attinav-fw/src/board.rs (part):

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//!
//! | function                         | pins                                   |
//! |----------------------------------|----------------------------------------|
//! | SPI1 → 3× RM3100                 | PA5 SCK, PA7 MOSI, PA6 MISO            |
//! | CS_MAG1..3 / DRDY_MAG1..3        | PC6 PC7 PC8 / PC9 PA8 PC10 (EXTI 9 8 10)|
//! | AVDD_EN1..3 (TPS22917, high = on)| PC11 PC12 PD2                          |
//! | TEMP_MAG1..3 (Pt1000 dividers)   | PC0 PC1 PC2 = ADC1_IN1..3              |
//! | SPI2 → 2× SCA3300 + ICM-42688-P  | PB13 SCK, PB15 MOSI, PB14 MISO         |
//! | CS_ACC1 CS_ACC2 CS_IMU / IMU_INT | PB4 PB5 PB6 / PB7 (EXTI 7)             |
//! | LPUART1 to the carrier           | PA2 TX, PA3 RX                         |
//! | QUIET (open drain, active low)   | PA15                                   |
//! | USB FS                           | PA11 DM, PA12 DP                       |
//! | status LED                       | PA0                                    |

use embassy_executor::Spawner;
use embassy_stm32::adc::{Adc, AdcChannel, AdcConfig, Averaging, Resolution};
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/// Hardware revision reported in `Info`.
pub const HARDWARE_REV: u8 = 2;

/// Rev B drives the status LED from PA0 through a series resistor to ground: **high = on**.
const LED_ON: Level = Level::High;
/// `QUIET` is an open-drain output pulled up on the carrier; asserted = driven low.
pub const QUIET_ASSERTED: Level = Level::Low;
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/// Peripherals of the carrier UART, kept aside until the stored baud rate is known.
pub struct UartParts {
    lpuart: embassy_stm32::Peri<'static, peripherals::LPUART1>,
    rx: embassy_stm32::Peri<'static, peripherals::PA3>,
    tx: embassy_stm32::Peri<'static, peripherals::PA2>,
    tx_dma: embassy_stm32::Peri<'static, peripherals::GPDMA1_CH4>,
    rx_dma: embassy_stm32::Peri<'static, peripherals::GPDMA1_CH5>,
}
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    let mut spi1_cfg = spi::Config::default();
    spi1_cfg.frequency = Hertz(1_000_000);
    spi1_cfg.mode = spi::MODE_0;
    let spi1 = Spi::new(p.SPI1, p.PA5, p.PA7, p.PA6, p.GPDMA1_CH0, p.GPDMA1_CH1, Irqs, spi1_cfg);
    let spi1 = SPI1_BUS.init(Mutex::new(spi1));
    fn cs(pin: embassy_stm32::Peri<'static, embassy_stm32::gpio::AnyPin>) -> Output<'static> {
        Output::new(pin, Level::High, Speed::VeryHigh)
    }
    let mags = Mags::new(
        [
            Rm3100::new(SpiDev::new(spi1, cs(p.PC6.into()))),
            Rm3100::new(SpiDev::new(spi1, cs(p.PC7.into()))),
            Rm3100::new(SpiDev::new(spi1, cs(p.PC8.into()))),
        ],
        [
            ExtiInput::new(p.PC9, p.EXTI9, Pull::Down, Irqs),
            ExtiInput::new(p.PA8, p.EXTI8, Pull::Down, Irqs),
            ExtiInput::new(p.PC10, p.EXTI10, Pull::Down, Irqs),
        ],
        [
            Output::new(p.PC11, Level::Low, Speed::Low),
            Output::new(p.PC12, Level::Low, Speed::Low),
            Output::new(p.PD2, Level::Low, Speed::Low),
        ],
    );

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    spi2_cfg.mode = spi::MODE_0;
    let spi2 = Spi::new(
        p.SPI2,
        p.PB13,
        p.PB15,
        p.PB14,
        p.GPDMA1_CH2,
        p.GPDMA1_CH3,
        Irqs,
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    let spi2 = SPI2_BUS.init(Mutex::new(spi2));
    let accels = Accels::new(
        [
            Sca3300::new(SpiDev::new(spi2, cs(p.PB4.into())), Delay),
            Sca3300::new(SpiDev::new(spi2, cs(p.PB5.into())), Delay),
        ],
        Icm42688::new(SpiDev::new(spi2, cs(p.PB6.into())), Delay),
        ExtiInput::new(p.PB7, p.EXTI7, Pull::None, Irqs),
    );

    // --- ADC1: Pt1000 dividers, 14 bit, 64× hardware averaging, VREFINT for the VDDA reading. ---
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            averaging: Some(Averaging::Samples64),
        },
    );
    let temps = Temps::new(adc, [p.PC0.degrade_adc(), p.PC1.degrade_adc(), p.PC2.degrade_adc()]);

    let quiet = OutputOpenDrain::new(p.PA15, Level::High, Speed::Low);
    let sensors = Sensors::new(mags, accels, temps, quiet);

    // --- Links. ---
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    let mut usb_cfg = usb::Config::default();
    // Bus powered through VBUS only; no VBUS sensing pin on the board.
    usb_cfg.vbus_detection = false;
    let usb_driver = usb::Driver::new_fs(p.USB_OTG_FS, Irqs, p.PA12, p.PA11, EP_OUT.init([0; 256]), usb_cfg);
    link::spawn_usb(spawner, usb_driver);

    let uart = UartParts {
        lpuart: p.LPUART1,
        rx: p.PA3,
        tx: p.PA2,
        tx_dma: p.GPDMA1_CH4,
        rx_dma: p.GPDMA1_CH5,
    };

    let led = Output::new(p.PA0, LED_ON, Speed::Low);

    Board {
        flash: p.FLASH,
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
